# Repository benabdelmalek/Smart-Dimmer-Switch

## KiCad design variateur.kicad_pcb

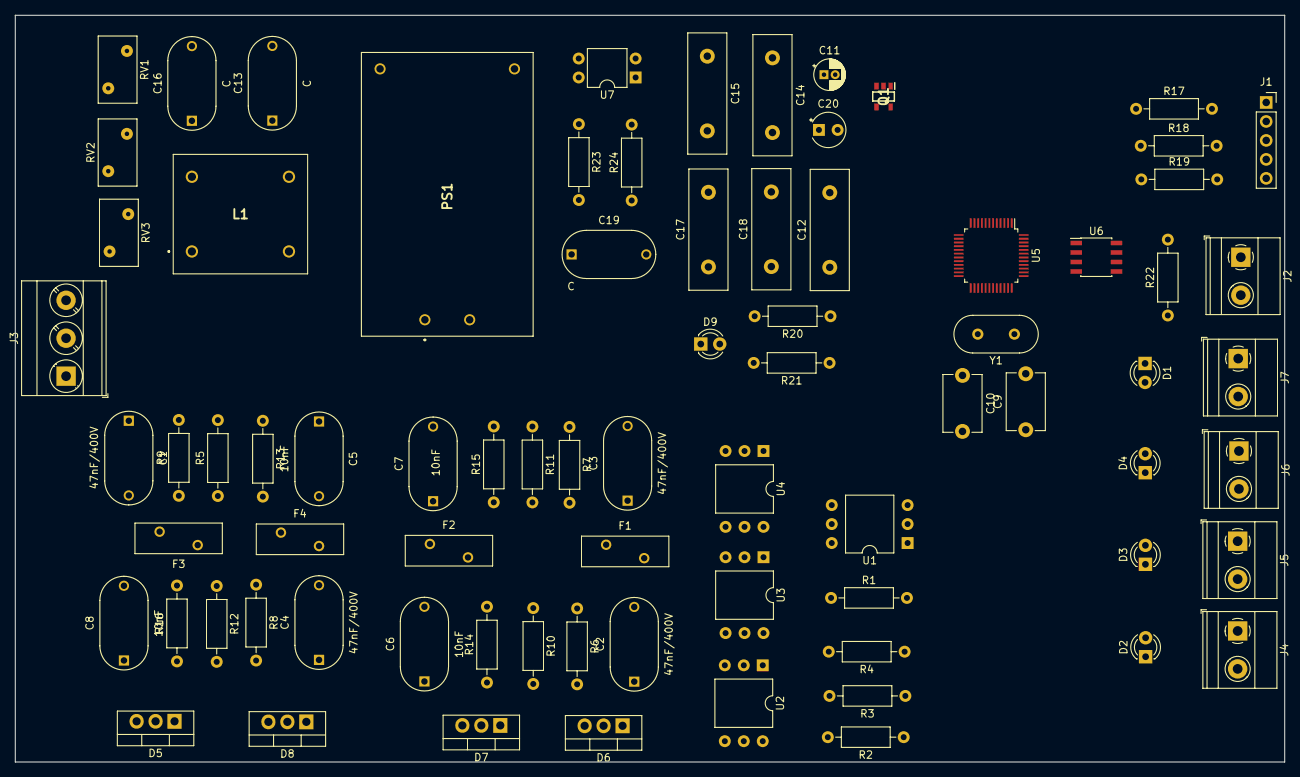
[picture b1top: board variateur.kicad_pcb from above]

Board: 2 copper layers, 170.0 x 100.0 mm, 78 parts (0 on the bottom side), 59 nets, no tracks yet.

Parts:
C1, C2, C3, C4: 47nF/400V; ECW-F4473JL
C5, C6, C7, C8: 10nF; ECW-F4473JL
C9, C10: 22pF; C_Disc_D7.5mm_W5.0mm_P7.50mm
C11: CP; CP_Radial_D4.0mm_P1.50mm
C12, C14, C15, C17, C18: 100nF; C_Disc_D16.0mm_W5.0mm_P10.00mm
C13, C16, C19: C; ECW-F4473JL
C20: 1uF; CP_Radial_Tantal_D4.5mm_P2.50mm
D1, D2, D3, D4: LED; LED_D3.0mm_Clear
D5, D6, D7, D8: BTA08-400BRG; TO-220-3_Vertical
D9: LED; LED_D3.0mm
F1, F2, F3, F4: Fuse; Fuse_BelFuse_0ZRE0033FF_L11.4mm_W3.8mm
J1: Conn_SWD; PinSocket_1x05_P2.54mm_Vertical
J2: CAN Connector; TerminalBlock_Phoenix_MKDS-1,5-2-5.08_1x02_P5.08mm_Horizont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
J3: Input; TerminalBlock_Phoenix_MKDS-3-3-5.08_1x03_P5.08mm_Horizontal
J4: Out1; TerminalBlock_Phoenix_MKDS-1,5-2-5.08_1x02_P5.08mm_Horizont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
J5: Out2; TerminalBlock_Phoenix_MKDS-1,5-2-5.08_1x02_P5.08mm_Horizont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
J6: Out3; TerminalBlock_Phoenix_MKDS-1,5-2-5.08_1x02_P5.08mm_Horizont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
J7: Out4; TerminalBlock_Phoenix_MKDS-1,5-2-5.08_1x02_P5.08mm_Horizont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
L1: L_Core; PLA10AN1522R0R2B
PS1: HLK-5M05; HLK5M05
Q1: XC6210B302MR-G; SOT95P280X120-5N
R1, R2, R3, R4, R23: 330; R_Axial_DIN0207_L6.3mm_D2.5mm_P10.16mm_Horizontal
R5, R6, R7, R8: 360; R_Axial_DIN0207_L6.3mm_D2.5mm_P10.16mm_Horizontal
R9, R10, R11, R12: 470; R_Axial_DIN0207_L6.3mm_D2.5mm_P10.16mm_Horizontal
R13, R14, R15, R16: 39; R_Axial_DIN0207_L6.3mm_D2.5mm_P10.16mm_Horizontal
R17, R18, R19, R20, R24: R; R_Axial_DIN0207_L6.3mm_D2.5mm_P10.16mm_Horizontal
R21: 10k; R_Axial_DIN0207_L6.3mm_D2.5mm_P10.16mm_Horizontal
R22: 120; R_Axial_DIN0207_L6.3mm_D2.5mm_P10.16mm_Horizontal
RV1, RV2, RV3: Varistor; RV_Disc_D9mm_W5.2mm_P5mm
U1, U2, U3, U4: MOC3021M; DIP-6_W10.16mm
U5: STM32F103C8Tx; LQFP-48_7x7mm_P0.5mm
U6: TJA1050T; SOIC-8_3.9x4.9mm_P1.27mm
U7: SFH620A-3X001; DIP-4_W7.62mm
Y1: 8MHz; Crystal_HC18-U_Vertical

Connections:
+5V: C11.1, PS1.4, Q1.1, Q1.3
/AC_F1: C13.1, C19.1, F1.1, F2.1, F3.1, F4.1, L1.1, PS1.1
/AC_F2: C13.2, J4.1, J5.1, J6.1, J7.1, L1.3, PS1.2, U7.2
/AC_Line1: C16.1, J3.1, L1.2, RV1.1, RV3.1
/AC_Line2: C16.2, J3.3, L1.4, RV1.2, RV2.1
/CANH: J2.1, R22.2, U6.7
/CANL: J2.2, R22.1, U6.6
/F1: D6.1, F1.2, R10.1, R14.2
/F2: D7.1, F2.2, R11.1, R15.2
/F3: D8.1, F3.2, R12.1, R16.2
/F4: D5.1, F4.2, R9.1, R13.2
/JTCK: R19.1, U5.37
/JTMS: R17.1, U5.34
/NRST: C12.2, R18.1, R21.2, U5.7
/ON1: R2.1, U5.14
/ON2: R3.1, U5.15
/ON3: R4.1, U5.16
/ON4: R1.1, U5.17
/OSC_IN: C9.1, U5.5, Y1.1
/OSC_OUT: C10.1, U5.6, Y1.2
/OUT_1: C2.2, C6.2, D6.2, J4.2
/OUT_2: C3.2, C7.2, D7.2, J5.2
/OUT_3: C4.2, C8.2, D8.2, J6.2
/OUT_4: C1.2, C5.2, D5.2, J7.2
/RxD: U5.32, U6.1
/TxD: U5.33, U6.4
/Zero: R23.1, U7.4
GND: C9.2, C10.2, C11.2, C12.1, C14.1, C15.1, C17.1, C18.1, C20.2, D1.1, D2.1, D3.1, D4.1, D9.1, J1.5, PS1.3, Q1.2, RV2.2, RV3.2, U5.8, U5.23, U5.35, U5.47, U6.2, U6.8, U7.3
unnamed: C1.1, R5.2, R9.2
unnamed: C2.1, R6.2, R10.2
unnamed: C3.1, R7.2, R11.2
unnamed: C4.1, R8.2, R12.2
unnamed: C5.1, R13.1
unnamed: C6.1, R14.1
unnamed: C7.1, R15.1
unnamed: C8.1, R16.1
unnamed: C19.2, R24.1
unnamed: D1.2, U1.2
unnamed: D2.2, U2.2
unnamed: D3.2, U3.2
unnamed: D4.2, U4.2
unnamed: D5.3, U1.4
unnamed: D6.3, U2.4
unnamed: D7.3, U3.4
unnamed: D8.3, U4.4
unnamed: D9.2, R20.2
unnamed: J1.2, R17.2
unnamed: J1.3, R18.2
unnamed: J1.4, R19.2
unnamed: R1.2, U1.1
unnamed: R2.2, U2.1
unnamed: R3.2, U3.1
unnamed: R4.2, U4.1
unnamed: R5.1, U1.6
unnamed: R6.1, U2.6
unnamed: R7.1, U3.6
unnamed: R8.1, U4.6
unnamed: R24.2, U7.1
VCC: C14.2, C15.2, C17.2, C18.2, C20.1, J1.1, Q1.5, R20.1, R21.1, R23.2, U5.1, U5.9, U5.24, U5.36, U5.48, U6.3

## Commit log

2020-04-21 remove folder
2020-04-21 first work

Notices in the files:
parts and their libraries:
Copyright 2016 Accelerated Designs. All rights reserved.
